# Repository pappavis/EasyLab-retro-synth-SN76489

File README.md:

## Chiptunes afspeel met Arduino ##
Lang gelede in die 1980's het ons grootgeword met 8-bit rekenaars soos BBC Micro B. Herleef die glorie en gebruik 'n BBC Micro geluidchip op Arduino | Raspberry Pi | Microbit.<br/>
<br/>
door: Michiel Erasmus<br/>
<br/>

## KiCAD 3d preview:
<br/>
<br/>

# User review
Buy online https://www.tindie.com/products/VliegendeVogel/arduino-soundcard-i2c-and-bbc-microbit-with-mml/

## Egte versie
Finale versie 0.7.06 <br>
<br/>

<br/>

## EasyLab4Kids

<br/><br/>
#e4kdenhaag<br/>

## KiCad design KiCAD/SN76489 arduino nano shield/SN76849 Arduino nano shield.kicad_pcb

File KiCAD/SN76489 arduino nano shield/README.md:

# EasyLab Muziek Editie #

Dit is 'n [Arduino][] shield vir [KiCad][] om muziek mee af te speel met gebruik van [SN76489][] geluids chip. <br/>
Die Sn76489 gebruik 'n 4.0000Mhz clock wat, of hardware clock osscilator kan wees, of gegenereerd met <a href="https://github.com/maxint-rd/FastPwmPin" target="_blank">FastPwmPin</a> van Maxint-RD.<br/>
<br/>
Features;<br/>
 - I2C aansluiting.<br/>
 - Gebruik arduino as clock op IO-poort 8.<br/>
 - Speel musiek af met MmlMusicPWM ook van MaxInt-RD.<br/>
 - Werkt met Arduino Nano, mega, Attiny85, D-MOS1 WiFi, Digispark USB, ESP8266-01 WiFi enz.

[KiCad]: http://www.kicad-pcb.org
[Arduino]: http://arduino.cc/
[SN76489]: https://nl.wikipedia.org/wiki/SN76489

## Hoe om te gebruik ##
 * Download Arduino IDE
 * Download en installeer Arduino biblioteek https://github.com/maxint-rd/mxUnifiedSN76489
 * Download en installeer Arduino biblioteek https://github.com/maxint-rd/mxUnifiedPCF8574
 * Met Arduino IDE. open voorbeeld Arduino/SN76489_met_PCF8574_arduino_clock_20180131.ino
  
## In deze argief ##

* KiCAD ontwerp
    * Die skema  en KiCAD model om 'n SN76489 geluidschip te gebruik.
* Printplaat schema
    * TODO -- gerber vir produksie
* 3D model
    * Voorbeeld van die model
* Bill of Materials
    * TODO
    
## License ##

Dit is 'n projek met GNU GPL version 3-lisensie.
usage of this PCB design should credit me as author. Thanks!

## Ontwikkelaar ##
2017-12-07 Origineel release<br/>
2017-06-02 Standalone I2C versie gebruikt.<br/>

<br/>\
#EasyLabMuziek #s4kdenhaag<br/>

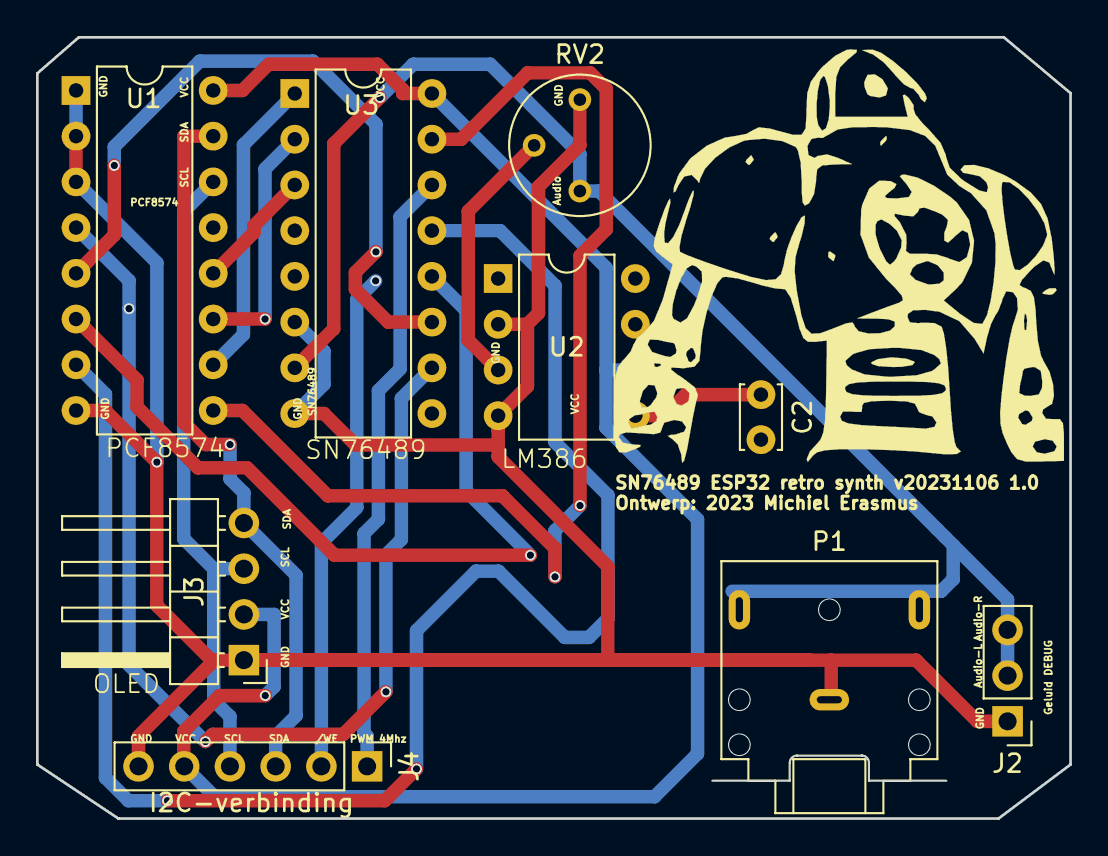
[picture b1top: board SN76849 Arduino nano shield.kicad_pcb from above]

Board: 2 copper layers, 57.4 x 43.4 mm, 10 parts (0 on the bottom side), 16 nets.

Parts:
C2: 250uF; C_Disc_D3.4mm_W2.1mm_P2.50mm
J2: audio_debug; PinHeader_1x03_P2.54mm_Vertical
J3: OLED_wit; PinHeader_1x04_P2.54mm_Horizontal
J4: ESP32Conn; PinHeader_1x06_P2.54mm_Vertical
J5: LOGO; Sovjet_simpits_logo01
P1: TRS_JACK; Jack_3.5mm_CUI_SJ1-3523N_Horizontal
RV2: Pot_10k; Potentiometer_Bourns_3339P_Vertical
U1: PCF8574; DIP-16_W7.62mm
U2: LM386; DIP-8_W7.62mm
U3: SN76489; DIP-16_W7.62mm

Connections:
/Audio: J2.2, J2.3, RV2.1, U3.7 (AUDIO_OUT)
/Clock: J4.1, U3.14 (CLOCK)
/P0: U1.4 (P0), U3.10 (D7)
/P1: U1.5 (P1), U3.11 (D6)
/P2: U1.6 (P2), U3.12 (D5)
/P3: U1.7 (P3), U3.13 (D4)
/P4: U1.9 (P4), U3.15 (D3)
/P5: U1.10 (P5), U3.1 (D2)
/P6: U1.11 (P6), U3.2 (D1)
/P7: U1.12 (P7), U3.3 (D0)
/SCL: J3.3, J4.4, U1.14 (SCL)
/SDA: J3.4, J4.3, U1.15 (SDA)
GND: J2.1, J3.1, J4.6, RV2.3, U1.1 (A0), U1.2 (A1), U1.3 (A2), U1.8 (VSS), U2.2 (-), U2.4 (GND), U3.8 (GND)
unnamed: C2.1, U2.5
unnamed: RV2.2, U2.3 (+)
VCC: J3.2, J4.5, U1.16 (VDD), U2.6 (V+), U3.16 (VCC)

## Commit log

2018-04-05 :circus_tent: Added .gitattributes & .gitignore files
2018-04-05 eerste commit
2018-04-05 PCF8574 netlist name bygewerkt na SN76489
2018-06-02 Printplaat 20180601 0.5 laat maak
2018-06-02 Printplaat 20180601 0.6 i2C silkS SDA toegevoegd
2018-06-18 toevoeging OpAmp schema en PCB 20180617 0.7
    daar is nog een bug. Op printplaat capacitor C1 posetief niet
    verobonden!
2018-06-24 DERC fails opgelost 20180617 0.7.01
    'n paar nets ontbreekte conneksies op de printplaat.
2018-06-24 toevoeging OpAmp schema en PCB 20180617 0.7.01
2018-06-24 Plaatje 20180617 0.7.01 bijgewerkt
2018-06-28 revisie 20180624 0.7.01 naar China
    silkscreen toegevoegd
2018-07-03 EasySynth 20180601 0.4 geassembleerd
2018-07-10 EasySynth SN87489 synth 0.7.01 printplaatversie
2018-07-19 20180719 0.7.03 OLED
    Groot bugfix;
    POTmeter verbinding
    LM358 nu dual op
    PWM pin is verbonde met LM358 out2
    Geluidsuitgang debug in stereo
    OLED skerm I2c toegevoegd.
2018-07-19 20180719 0.7.03 OLED
2018-07-20 bij20180719 0.7.03 OLED
2018-08-07 voorbeeld met FastPWM 20180807 0.7.05
2018-09-03 Upgrade project naar KiCAD 4.0.0
2018-09-05 versie 20180905 0.7.06
    LM358 opAmp wasverwyderd,
    Dip-14 Xtal clock 4Mhz toegevoegd.
2018-09-08 versie 20180905 0.7.06
2023-02-28 Use CHATGPT to write to the SN76489 via I2C
2023-02-28 Rename sn76489_mml.py to sn76489.py
2023-02-28 To use this class library, simply create an instance of VGMPlayer and call its `play
    To use this class library, simply create an instance of VGMPlayer and call its `play
2023-02-28 MML file for the first 30 seconds of Commando by Rob Hubbard using at least 3 voices for the YM3812
    MML file for the first 30 seconds of Commando by Rob Hubbard using at least 3 voices for the YM3812
2023-02-28 first 30 seconds of the chiptune Commando by Rob Hubbard in a MML-file format for SN76489
    The MML code specifies the chip as SN76489 and sets the tempo to 150 BPM. The music is written in 8th note duration and in octave 4. The tune is split into three voices, with Voice 1 playing the main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
2023-02-28 the first 15 seconds of the chiptune Commando by Rob Hubbard and play it using 3 analoge pins on a ESP32
    This code snippet generates a simple square wave with a frequency of 440Hz and a duty cycle of 50%, and outputs it to 3 different analog pins (pins 26, 27, and 32). It then defines a melody (the firs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
    Note that this code is only a simple example and may need to be modified to produce the desired sound and to
2023-03-01 Plays midi files on SN76489 using I2C
2023-03-01 Rename sn76489_midi.py to sn76489midi.py
2023-04-07 sn67489 I2c van https://github.com/Kyuchumimo/micropython-sn76489
2023-10-26 Bijgewerkt naar KiCAD 7.0
2023-11-01 Algemeen bijgewerkt
2023-11-07 Bijgewerkt
2023-11-13 bijgewerkt2
2024-01-05 PCB gerbers naar jlcpcb.com
2025-02-18 COnverted to KiCAD8

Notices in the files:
KiCAD/SN76489 arduino nano shield/SN76849 Arduino nano shield.kicad_pcb:
©2018 EasyLab4Kids en Michiel Erasmus
